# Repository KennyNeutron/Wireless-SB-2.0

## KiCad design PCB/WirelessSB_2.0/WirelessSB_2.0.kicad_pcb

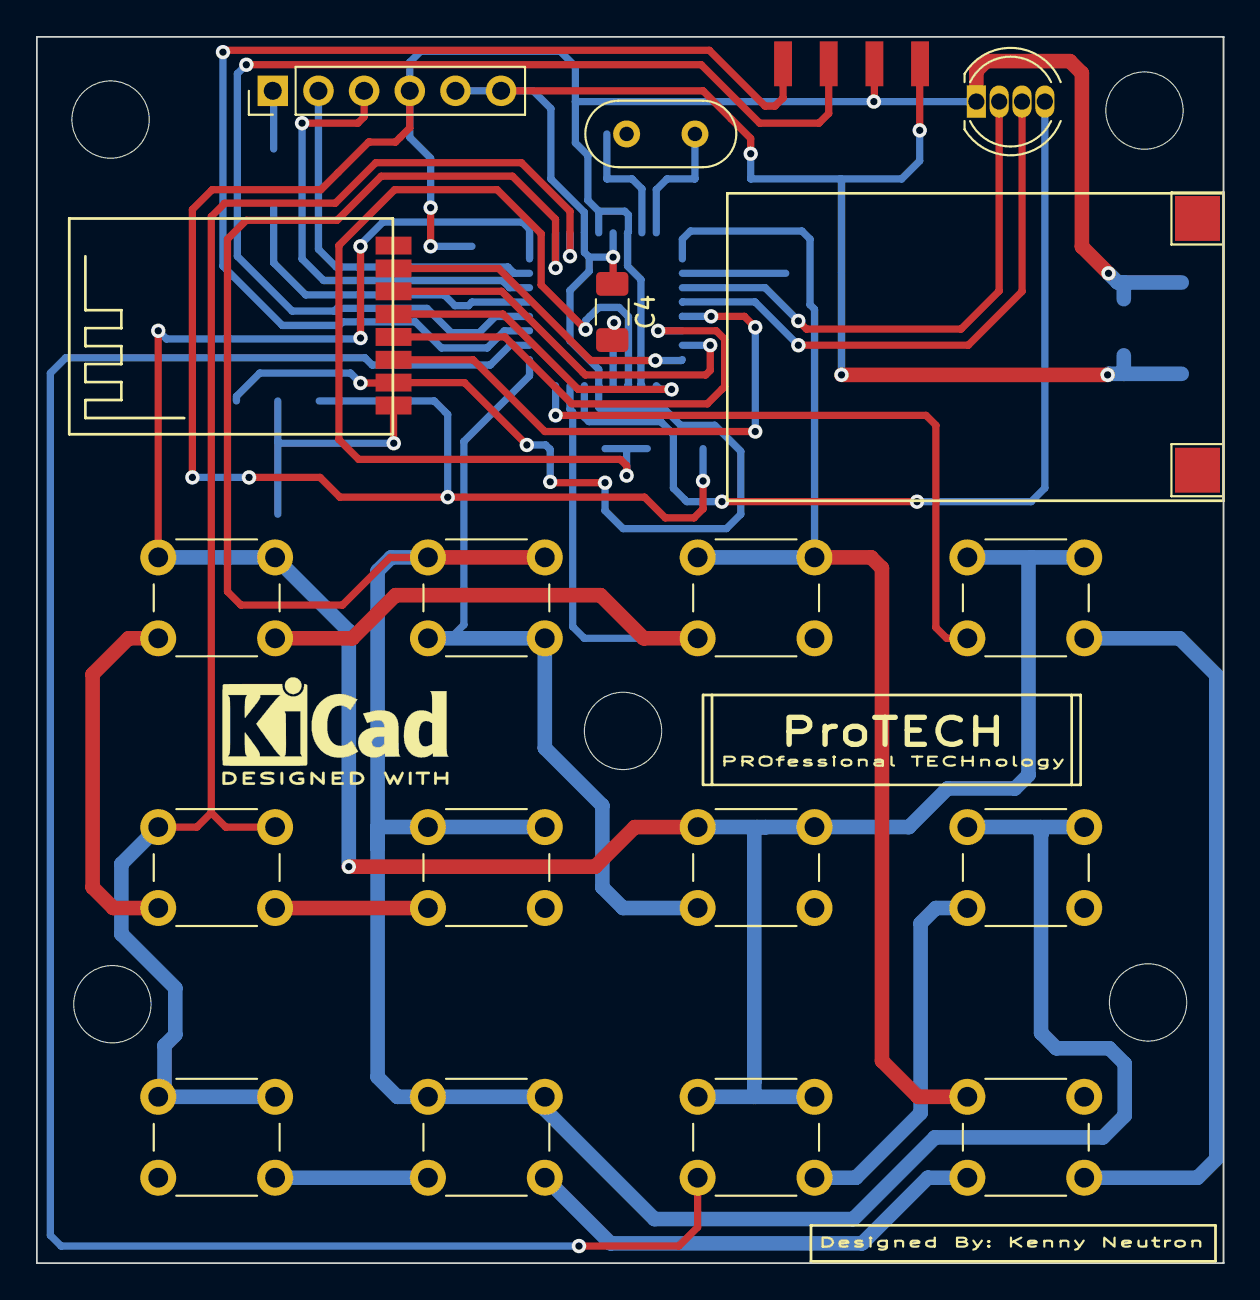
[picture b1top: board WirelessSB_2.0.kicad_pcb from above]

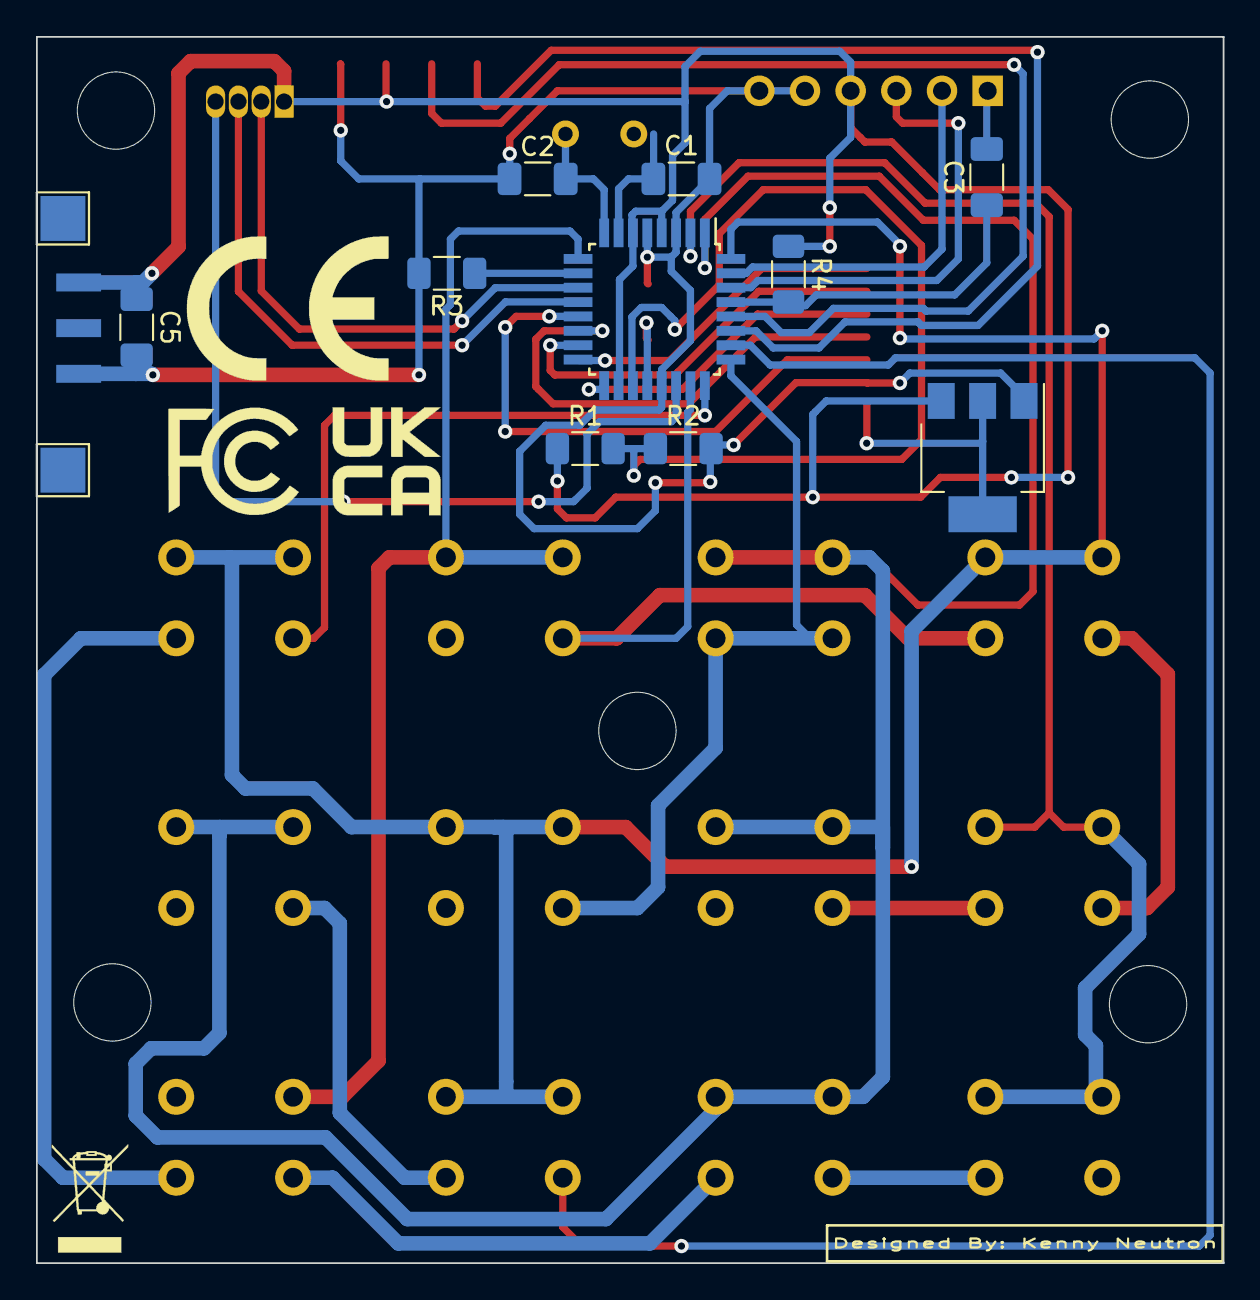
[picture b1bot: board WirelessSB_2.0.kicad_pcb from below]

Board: 2 copper layers, 66.0 x 68.2 mm, 29 parts (11 on the bottom side), 30 nets.

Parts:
C1, C2: 22pF; C_1206_3216Metric_Pad1.33x1.80mm_HandSolder
C3, C4, C5: 100nF; C_1206_3216Metric_Pad1.33x1.80mm_HandSolder
D1: LED_ARGB; LED_D5.0mm-4_RGB
J1: Battery+Switch; Harwin_M20-89003xx_1x03_P2.54mm_Horizontal
J2: OLED Display; Harwin_M20-89004xx_1x04_P2.54mm_Horizontal(2)
J3: FTDI Programmer; PinHeader_1x06_P2.54mm_Vertical
R1: 330R; R_1206_3216Metric_Pad1.30x1.75mm_HandSolder
R2: 100R; R_1206_3216Metric_Pad1.30x1.75mm_HandSolder
R3, R4: 1K; R_1206_3216Metric_Pad1.30x1.75mm_HandSolder
SW1: PB1(Shift); SW_PUSH_6mm_H4.3mm
SW2: PB5(HFoul); SW_PUSH_6mm_H4.3mm
SW3: PB9(HScore); SW_PUSH_6mm_H4.3mm
SW4: PB13(R24); SW_PUSH_6mm_H4.3mm
SW5: PB2(Buzzer); SW_PUSH_6mm_H4.3mm
SW6: PB6(GFoul); SW_PUSH_6mm_H4.3mm
SW7: PB10(GScore); SW_PUSH_6mm_H4.3mm
SW8: PB14(StartStop); SW_PUSH_6mm_H4.3mm
SW9: PB3(HTOut); SW_PUSH_6mm_H4.3mm
SW10: PB7(R14); SW_PUSH_6mm_H4.3mm
SW13: PB4(GTOut); SW_PUSH_6mm_H4.3mm
SW14: PB8(Pos); SW_PUSH_6mm_H4.3mm
U1: ATmega328P-A; TQFP-32_7x7mm_P0.8mm
U2: AMS1117-3.3; SOT-223-3_TabPin2
U3: NRF24L01_Breakout; NRF24L01-SMD
Y1: Crystal; Crystal_HC52-6mm_Vertical

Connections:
+3V3: U2.2 (VO), U3.2 (VCC)
CSN: U1.14 (PB2), U3.4 (~CSN)
DTR: C3.1, R4.2, U1.29 (~RESET/PC6)
FTDI_RX: J3.2, U1.31 (PD1)
FTDI_TX: J3.3, U1.30 (PD0)
GND: C1.2, C2.2, C4.1, C5.2, J1.1, J2.4, J3.5, J3.6, R2.2, R3.2, U1.3 (GND), U1.5 (GND), U1.21 (GND), U2.1 (GND), U3.1 (GND)
LED_RGB_B: D1.4 (BK), U1.22 (ADC7)
LED_RGB_G: D1.3 (GK), U1.12 (PB0)
LED_RGB_R: D1.2 (RK), U1.11 (PD7)
MISO: U1.16 (PB4), U3.7 (MISO)
MOSI: U1.15 (PB3), U3.6 (MOSI)
NCE: U1.13 (PB1), U3.3 (CE)
unnamed: C1.1, U1.7 (XTAL1/PB6), Y1.2
unnamed: C2.1, U1.8 (XTAL2/PB7), Y1.1
unnamed: C3.2, J3.1
unnamed: C4.2, U1.20 (AREF)
unnamed: R3.1, U1.10 (PD6)
unnamed: R1.2, R2.1, U1.19 (ADC6)
SCK: U1.17 (PB5), U3.5 (SCK)
SCL: J2.2, U1.28 (PC5)
SDA: J2.1, U1.27 (PC4)
SW_C1: SW1.2, SW2.2, SW3.2, SW4.2, U1.23 (PC0)
SW_C2: SW5.2, SW6.2, SW7.2, SW8.2, U1.24 (PC1)
SW_C3: SW9.2, SW10.2, U1.25 (PC2)
SW_C4: SW13.2, SW14.2, U1.26 (PC3)
SW_R1: SW1.1, SW5.1, SW9.1, SW13.1, U1.32 (PD2)
SW_R2: SW2.1, SW6.1, SW10.1, SW14.1, U1.1 (PD3)
SW_R3: SW3.1, SW7.1, U1.2 (PD4)
SW_R4: SW4.1, SW8.1, U1.9 (PD5)
VCC: C5.1, D1.1 (A), J1.3, J2.3, J3.4, R1.1, R4.1, U1.4 (VCC), U1.6 (VCC), U1.18 (AVCC), U2.3 (VI)

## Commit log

2022-10-09 Done with the Controller main PCB
2022-10-09 FIXED: moved the BatteryIN & Capacitor to the bottom layer as it hits the charge controller
2022-10-12 ADJUSTED: schematic diagram (ocd things :D) and ADDED: pdf file of the schematic from KiCAD
